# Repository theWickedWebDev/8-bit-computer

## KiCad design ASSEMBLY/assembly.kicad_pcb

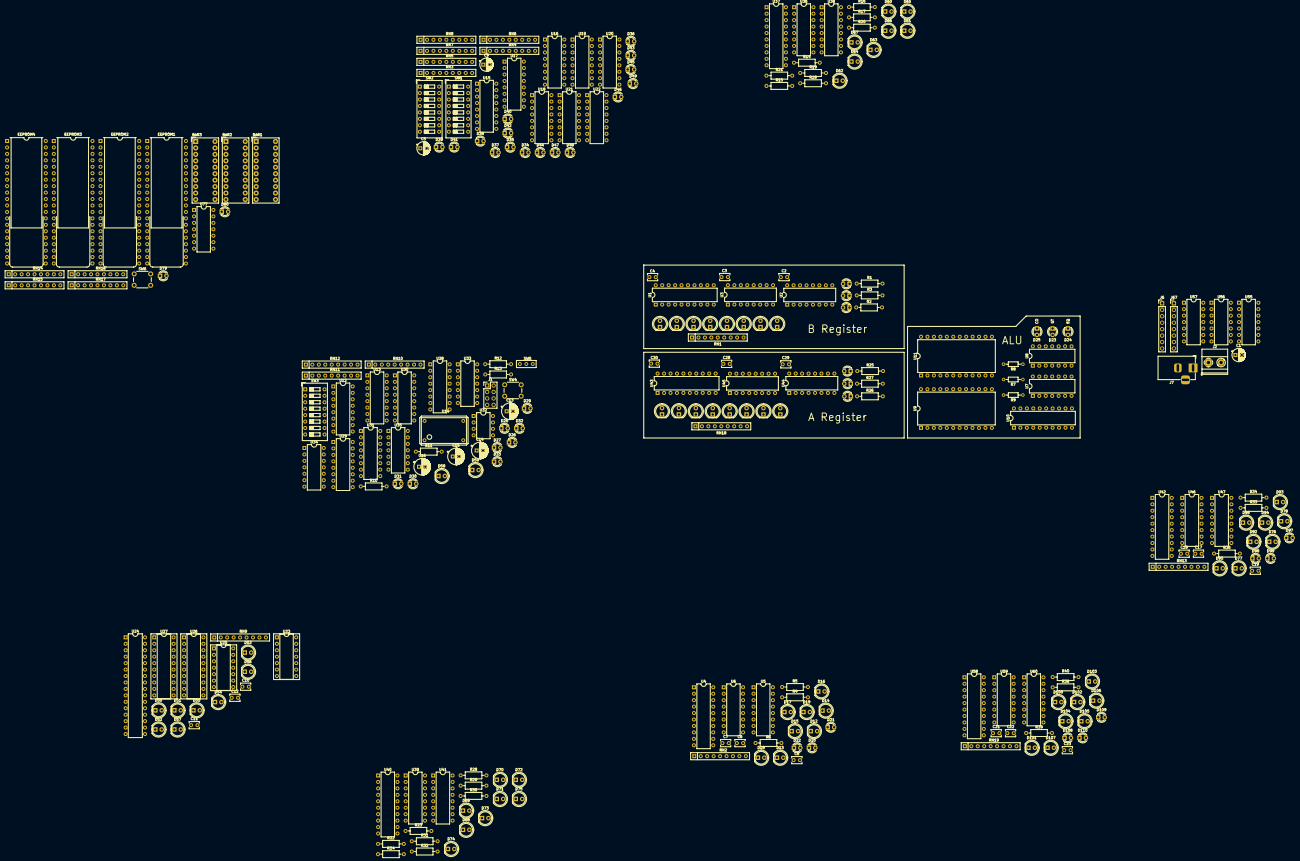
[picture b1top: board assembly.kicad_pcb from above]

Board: 2 copper layers, 264 parts (0 on the bottom side), 344 nets, no tracks yet.

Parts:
BAR1, BAR2, BAR3: HDSP-4850_2; HDSP-4850
C1, C5, C9: CP1_Small; CP_Radial_D5.0mm_P2.50mm
C2, C3, C4, C6, C7, C8, C17, C18, C19, C21, C22, C23, C28, C29, C30: CP1; C_Disc_D3.8mm_W2.6mm_P2.50mm
C10, C11, C12: C_Small; C_Disc_D3.8mm_W2.6mm_P2.50mm
C13, C14, C15, C16: CP1; CP_Radial_D6.3mm_P2.50mm
D1, D2, D3, D4, D5, D6, D7, D8, D12, D13, D14, D15, D16, D17, D18, D19, D50, D51, D52, D53, D54, D55, D56, D57, D58, D59, D60, D61, D62, D63, D64, D65, D66, D67, D68, D69, D70, D71, D72, D73, D74, D75, D76, D77, D78, D81, D82, D83, D84, D85, D86, D87, D88, D92, D93, D94, D95, D96, D100, D101, D102, D103, D104, D105, D106, D107: LED; LED_D5.0mm
D9, D10, D11, D20, D21, D22, D23, D24, D25, D26, D27, D28, D29, D30, D31, D32, D33, D34, D35, D36, D37, D38, D39, D40, D41, D42, D43, D44, D45, D46, D47, D48, D49, D79, D80, D89, D90, D91, D97, D98, D99, D108, D109, D110: LED; LED_D3.0mm
EEPROM1, EEPROM2, EEPROM3, EEPROM4: AT28C256; EEPROM_Socket_lever
J1: Conn_01x04; PinHeader_2x04_P2.54mm_Vertical
J2: Screw_Terminal_01x02; TerminalBlock_Phoenix_MKDS-1,5-2_1x02_P5.00mm_Horizontal
J6, J67: Conn_01x08; PinHeader_1x08_P2.54mm_Vertical
J7: Barrel_Jack_MountingPin; BarrelJack_Horizontal
R1, R2, R3, R4, R5, R6, R10, R11, R12, R13, R25, R26, R27, R33, R34, R35, R38, R39, R40: R_Small_US; R_Axial_DIN0207_L6.3mm_D2.5mm_P10.16mm_Horizontal
R7, R8, R9: R_Small_US; R_Axial_DIN0204_L3.6mm_D1.6mm_P7.62mm_Horizontal
R14, R15, R16, R17, R18, R19, R20, R21, R22, R23, R24, R28, R29, R30, R31, R32: R_US; R_Axial_DIN0207_L6.3mm_D2.5mm_P10.16mm_Horizontal
RN1, RN2, RN13, RN18, RN19: R_Network08; R_Array_SIP9
RN3, RN4, RN5, RN6, RN7, RN8, RN9, RN10, RN11, RN12, RN14, RN15, RN16, RN17: R_Network08_US; R_Array_SIP9
SW1, SW2, SW3: SW_DIP_x08; SW_DIP_SPSTx08_Slide_9.78x22.5mm_W7.62mm_P2.54mm
SW4, SW6: SW_Push; SW_PUSH_6mm
SW5: SW_SPDT; SPDT-SlideSwitch
U1, U4, U10, U37, U40, U42, U43, U58: 74LS245; DIP-20_W7.62mm
U2, U3, U5, U6, U12, U13, U16, U17, U20, U21, U44, U45, U46, U47, U59, U60: 74LS173; DIP-16_W7.62mm
U7, U33, U55, U56, U57, U77: 74LS04; DIP-14_W7.62mm
U8: 74LS02; DIP-14_W7.62mm
U9, U11: 74LS181; DIP-24_W15.24mm
U14: 4-pin-crystal-1mhz; full_can _1mhz_crystal
U15, U18, U19, U22: 74LS157; DIP-16_W7.62mm
U23: 74LS00; DIP-14_W7.62mm_Socket
U24: IS61C1024-15N; DIP-32_W7.62mm
U25: 74LS32; DIP-14_W7.62mm_Socket
U26, U27: 74LS245; DIP-20_W7.62mm_Socket
U28, U29, U30, U31: 74LS193; DIP-16_W7.62mm
U32: LM555xN; DIP-8_W7.62mm
U34: 74LS08; DIP-14_W7.62mm
U35: 74LS86; DIP-14_W7.62mm
U36, U38, U39, U41: 74LS161; DIP-16_W7.62mm

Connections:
/Sheet60DC0D37/MANUAL_MEM_ADR_00: RN7.2, SW2.16, U15.13
/Sheet60DC0D37/MANUAL_MEM_ADR_01: RN7.3, SW2.15, U15.10
/Sheet60DC0D37/MANUAL_MEM_ADR_02: RN7.4, SW2.14, U15.6
/Sheet60DC0D37/MANUAL_MEM_ADR_03: RN7.5, SW2.13, U15.3
/Sheet60DC0D37/MANUAL_MEM_ADR_04: RN7.6, SW2.12, U18.13
/Sheet60DC0D37/MANUAL_MEM_ADR_05: RN7.7, SW2.11, U18.10
/Sheet60DC0D37/MANUAL_MEM_ADR_06: RN7.8, SW2.10, U18.6
/Sheet60DC0D37/MANUAL_MEM_ADR_07: RN7.9, SW2.9, U18.3
/Sheet60DC0D37/MANUAL_MEM_ADR_08: RN5.2, SW1.16, U19.13
/Sheet60DC0D37/MANUAL_MEM_ADR_09: RN5.3, SW1.15, U19.10
/Sheet60DC0D37/MANUAL_MEM_ADR_10: RN5.4, SW1.14, U19.6
/Sheet60DC0D37/MANUAL_MEM_ADR_11: RN5.5, SW1.13, U19.3
/Sheet60DC0D37/MANUAL_MEM_ADR_12: RN5.6, SW1.12, U22.13
/Sheet60DC0D37/MANUAL_MEM_ADR_13: RN5.7, SW1.11, U22.10
/Sheet60DC0D37/MANUAL_MEM_ADR_14: RN5.8, SW1.10, U22.6
/Sheet60DC0D37/MANUAL_MEM_ADR_15: RN5.9, SW1.9, U22.3
/Sheet60DC0D37/MAR_00: U15.14, U21.3
/Sheet60DC0D37/MAR_01: U15.11, U21.4
/Sheet60DC0D37/MAR_02: U15.5, U21.5
/Sheet60DC0D37/MAR_03: U15.2, U21.6
/Sheet60DC0D37/MAR_04: U18.14, U20.3
/Sheet60DC0D37/MAR_05: U18.11, U20.4
/Sheet60DC0D37/MAR_06: U18.5, U20.5
/Sheet60DC0D37/MAR_07: U18.2, U20.6
/Sheet60DC0D37/MAR_08: U17.3, U19.14
/Sheet60DC0D37/MAR_09: U17.4, U19.11
/Sheet60DC0D37/MAR_10: U17.5, U19.5
/Sheet60DC0D37/MAR_11: U17.6, U19.2
/Sheet60DC0D37/MAR_12: U16.3, U22.14
/Sheet60DC0D37/MAR_13: U16.4, U22.11
/Sheet60DC0D37/MAR_14: U16.5, U22.5
/Sheet60DC0D37/MAR_15: U16.6, U22.2
/Sheet60E7756D/IO0: D57.2, U24.13, U26.18, U27.2
/Sheet60E7756D/IO1: D56.2, U24.14, U26.17, U27.3
/Sheet60E7756D/IO2: D55.2, U24.15, U26.16, U27.4
/Sheet60E7756D/IO3: D54.2, U24.17, U26.15, U27.5
/Sheet60E7756D/IO4: D53.2, U24.18, U26.14, U27.6
/Sheet60E7756D/IO5: D52.2, U24.19, U26.13, U27.7
/Sheet60E7756D/IO6: D51.2, U24.20, U26.12, U27.8
/Sheet60E7756D/IO7: D50.2, U24.21, U26.11, U27.9
/Sheet613FD1FC/D32: D80.2, EEPROM4.19, SW6.1, U77.1
/Sheet613FD1FC/STEP1: EEPROM1.10, EEPROM2.10, EEPROM3.10, EEPROM4.10, U40.9
/Sheet613FD1FC/STEP2: EEPROM1.9, EEPROM2.9, EEPROM3.9, EEPROM4.9, U40.8
/Sheet613FD1FC/STEP3: EEPROM1.8, EEPROM2.8, EEPROM3.8, EEPROM4.8, U40.7
/Sheet613FD1FC/μ28: BAR3.3, EEPROM4.15
/Sheet613FD1FC/μ29: BAR3.2, EEPROM4.16
/Sheet613FD1FC/μ30: BAR3.1, EEPROM4.17
/Sheet634DE12C/1MHz_Pulse: U12.7, U13.7, U14.8, U28.4
/Sheet634DE12C/A0: D26.2, U12.3, U28.15
/Sheet634DE12C/A1: D27.2, U12.4, U28.1
/Sheet634DE12C/A2: D28.2, U12.5, U28.10
/Sheet634DE12C/A3: D29.2, U12.6, U28.9
/Sheet634DE12C/A4: D30.2, U13.3, U29.15
/Sheet634DE12C/A5: D31.2, U13.4, U29.1
/Sheet634DE12C/A6: D32.2, U13.5, U29.10
/Sheet634DE12C/A7: D33.2, U13.6, U29.9
/μ1: BAR1.10, EEPROM1.11, U57.13
/μ2: BAR1.9, EEPROM1.12, U57.11
/μ3: BAR1.8, EEPROM1.13, U57.9
/μ4: BAR1.7, EEPROM1.15, U57.5
/μ5: BAR1.6, EEPROM1.16, U57.3
/μ6: BAR1.5, EEPROM1.17, U57.1
/μ7: BAR1.4, EEPROM1.18, U56.13
/μ8: BAR1.3, EEPROM1.19, U56.11
/μ9: BAR1.2, EEPROM2.11, U56.9
/μ10: BAR1.1, EEPROM2.12, U56.5
/μ11: BAR2.10, EEPROM2.13, U56.3
/μ12: BAR2.9, EEPROM2.15, U56.1
/μ13: BAR2.8, EEPROM2.16, U55.13
/μ14: BAR2.7, EEPROM2.17, U55.11
/μ15: BAR2.6, EEPROM2.18, U55.9
/μ16: BAR2.5, EEPROM2.19, U55.5
/μ17: BAR2.4, EEPROM3.11, U55.3
/μ18: BAR2.3, EEPROM3.12, U55.1
A0: D49.2, U15.12, U24.12
A1: D48.2, U15.9, U24.11
A2: D47.2, U15.7, U24.10
A3: D46.2, U15.4, U24.9
A4: D45.2, U18.12, U24.8
A5: D44.2, U18.9, U24.7
A6: D43.2, U18.7, U24.6
A7: D42.2, U18.4, U24.5
A8: D41.2, U19.12, U24.27
A9: D40.2, U19.9, U24.26
A10: D39.2, U19.7, U24.23
A11: D38.2, U19.4, U24.25
A12: D37.2, U22.12, U24.4
A13: D36.2, U22.9, U24.28
A14: D35.2, U22.7, U24.3
A15: D34.2, U22.4, U24.31
A16: C1.2, C2.2, C3.2, C4.2, C5.2, C6.2, C7.2, C8.2, C9.2, C10.2, C11.2, C12.2, C15.2, C16.2, C17.2, C18.2, C19.2, C21.2, C22.2, C23.2, C28.2, C29.2, C30.2, EEPROM1.4, EEPROM1.14, EEPROM1.20, EEPROM1.22, EEPROM2.4, EEPROM2.14, EEPROM2.20, EEPROM2.22, EEPROM3.4, EEPROM3.14, EEPROM3.20, EEPROM3.22, EEPROM4.4, EEPROM4.14, EEPROM4.20, EEPROM4.22, J2.1, J7.2, R1.2, R2.2, R3.2, R4.2, R5.2, R6.2, R7.2, R8.2, R9.2, R10.2, R13.2, R14.2, R15.2, R16.2, R17.2, R18.2, R19.2, R20.2, R21.2, R22.2, R23.2, R24.2, R25.2, R26.2, R27.2, R28.2, R29.2, R30.2, R31.2, R32.2, R33.2, R34.2, R35.2, R38.2, R39.2, R40.2, RN1.1, RN2.1, RN3.1, RN4.1, RN5.1, RN7.1, RN9.1, RN10.1, RN12.1, RN13.1, RN14.1, RN15.1, RN16.1, RN17.1, RN18.1, RN19.1, SW4.1, SW5.1, U1.10, U2.1, U2.2, U2.8, U3.1, U3.2, U3.8, U4.10, U5.1, U5.2, U5.8, U6.1, U6.2, U6.8, U7.7, U8.7, U9.12, U10.1, U10.10, U11.12, U12.1, U12.2, U12.8, U12.15, U13.1, U13.2, U13.8, U13.15, U14.7, U15.8, U15.15, U16.1, U16.2, U16.8, U17.1, U17.2, U17.8, U18.8, U18.15, U19.8, U19.15, U20.1, U20.2, U20.8, U21.1, U21.2, U21.8, U22.8, U22.15, U23.7, U24.2, U24.16, U24.22, U24.24, U25.7, U26.10, U27.10, U28.8, U28.14, U29.8, U29.14, U30.1, U30.8, U30.9, U30.10, U30.14, U30.15, U31.8, U31.14, U32.1, U33.7, U34.7, U35.7, U36.8, U37.1, U37.10, U38.8, U39.8, U40.1, U40.10, U40.19, U41.8, U42.10, U43.10, U44.1, U44.2, U44.8, U45.1, U45.2, U45.8, U46.1, U46.2, U46.8, U47.1, U47.2, U47.8, U55.7, U56.7, U57.7, U58.10, U59.1, U59.2, U59.8, U60.1, U60.2, U60.8, U77.7, U77.9, U77.11, U77.13
ALU0: BAR2.2, EEPROM3.13, U9.6, U11.6
ALU1: BAR2.1, EEPROM3.15, U9.5, U11.5
ALU2: BAR3.10, EEPROM3.16, U9.4, U11.4
ALU3: BAR3.9, EEPROM3.17, U9.3, U11.3
ALU_MODE: BAR3.8, EEPROM3.18, U9.8, U11.8
ALU_OUT: U10.19, U56.2
A_IN: BAR3.5, D10.2, D21.2, D90.2, D98.2, D109.2, U2.9, U2.10, U3.9, U3.10, U5.9, U5.10, U6.9, U6.10, U44.9, U44.10, U45.9, U45.10, U46.9, U46.10, U47.9, U47.10, U55.8, U56.4, U56.8, U57.8, U59.9, U59.10, U60.9, U60.10, U77.4
A_OUT: BAR3.4, D11.2, D22.2, D91.2, D99.2, D110.2, U1.19, U4.19, U42.19, U43.19, U55.10, U56.6, U56.10, U57.10, U58.19, U77.6
BUS0: J6.1, J67.1, RN10.2, SW3.16, U1.11, U3.11, U4.11, U6.11, U10.9, U12.14, U17.14, U21.14, U27.18, U38.3, U41.3, U42.11, U43.11, U45.11, U47.11, U58.11, U60.11
BUS1: J6.2, J67.2, RN10.3, SW3.15, U1.12, U3.12, U4.12, U6.12, U10.8, U12.13, U17.13, U21.13, U27.17, U38.4, U41.4, U42.12, U43.12, U45.12, U47.12, U58.12, U60.12
BUS2: J6.3, J67.3, RN10.4, SW3.14, U1.13, U3.13, U4.13, U6.13, U10.7, U12.12, U17.12, U21.12, U27.16, U38.5, U41.5, U42.13, U43.13, U45.13, U47.13, U58.13, U60.13
BUS3: J6.4, J67.4, RN10.5, SW3.13, U1.14, U3.14, U4.14, U6.14, U10.6, U12.11, U17.11, U21.11, U27.15, U38.6, U41.6, U42.14, U43.14, U45.14, U47.14, U58.14, U60.14
BUS4: J6.5, J67.5, RN10.6, SW3.12, U1.15, U2.11, U4.15, U5.11, U10.5, U13.14, U16.14, U20.14, U27.14, U36.6, U39.3, U42.15, U43.15, U44.11, U46.11, U58.15, U59.11
BUS5: J6.6, J67.6, RN10.7, SW3.11, U1.16, U2.12, U4.16, U5.12, U10.4, U13.13, U16.13, U20.13, U27.13, U36.5, U39.4, U42.16, U43.16, U44.12, U46.12, U58.16, U59.12
BUS6: J6.7, J67.7, RN10.8, SW3.10, U1.17, U2.13, U4.17, U5.13, U10.3, U13.12, U16.12, U20.12, U27.12, U36.4, U39.5, U42.17, U43.17, U44.13, U46.13, U58.17, U59.13
BUS7: J6.8, J67.8, RN10.9, SW3.9, U1.18, U2.14, U4.18, U5.14, U10.2, U13.11, U16.11, U20.11, U27.11, U36.3, U39.6, U42.18, U43.18, U44.14, U46.14, U58.18, U59.14
CARRY: D25.2, EEPROM1.5, EEPROM2.5, EEPROM3.5, EEPROM4.5, U7.2
CLOCK: D59.2, U2.7, U3.7, U5.7, U6.7, U16.7, U17.7, U20.7, U21.7, U25.2, U35.3, U36.2, U38.2, U39.2, U41.2, U44.7, U45.7, U46.7, U47.7, U59.7, U60.7
D0: D1.2, D12.2, D76.2, D81.2, D100.2, EEPROM1.3, EEPROM2.3, EEPROM3.3, EEPROM4.3, U1.9, U3.6, U4.9, U6.6, U11.1, U11.2, U26.2, U42.9, U43.9, U45.6, U47.6, U58.9, U60.6
D1: D2.2, D13.2, D77.2, D82.2, D101.2, EEPROM1.25, EEPROM2.25, EEPROM3.25, EEPROM4.25, U1.8, U3.5, U4.8, U6.5, U11.22, U11.23, U26.3, U42.8, U43.8, U45.5, U47.5, U58.8, U60.5
D2: D3.2, D14.2, D78.2, D83.2, D102.2, EEPROM1.24, EEPROM2.24, EEPROM3.24, EEPROM4.24, U1.7, U3.4, U4.7, U6.4, U11.20, U11.21, U26.4, U42.7, U43.7, U45.4, U47.4, U58.7, U60.4
D3: D4.2, D15.2, D84.2, D92.2, D103.2, EEPROM1.21, EEPROM2.21, EEPROM3.21, EEPROM4.21, U1.6, U3.3, U4.6, U6.3, U11.18, U11.19, U26.5, U42.6, U43.6, U45.3, U47.3, U58.6, U60.3
D4: D5.2, D16.2, D85.2, D93.2, D104.2, EEPROM1.23, EEPROM2.23, EEPROM3.23, EEPROM4.23, U1.5, U2.6, U4.5, U5.6, U9.1, U9.2, U26.6, U42.5, U43.5, U44.6, U46.6, U58.5, U59.6
D5: D6.2, D17.2, D86.2, D94.2, D105.2, EEPROM1.2, EEPROM2.2, EEPROM3.2, EEPROM4.2, U1.4, U2.5, U4.4, U5.5, U9.22, U9.23, U26.7, U42.4, U43.4, U44.5, U46.5, U58.4, U59.5
D6: D7.2, D18.2, D87.2, D95.2, D106.2, EEPROM1.26, EEPROM2.26, EEPROM3.26, EEPROM4.26, U1.3, U2.4, U4.3, U5.4, U9.20, U9.21, U26.8, U42.3, U43.3, U44.4, U46.4, U58.3, U59.4
D7: D8.2, D19.2, D88.2, D96.2, D107.2, EEPROM1.1, EEPROM2.1, EEPROM3.1, EEPROM4.1, U1.2, U2.3, U4.2, U5.3, U9.18, U9.19, U26.9, U42.2, U43.2, U44.3, U46.3, U58.2, U59.3
EQ: D24.2, EEPROM1.6, EEPROM2.6, EEPROM3.6, EEPROM4.6, U8.6, U9.14, U11.14
GT: D23.2, EEPROM1.7, EEPROM2.7, EEPROM3.7, EEPROM4.7, U8.4
HALT: D79.2, EEPROM4.18, U34.5, U34.9
MAR1_IN: U16.9, U16.10, U17.9, U17.10, U57.4
MAR2_IN: U20.9, U20.10, U21.9, U21.10, U57.2
unnamed: BAR1.11, RN14.9
unnamed: BAR1.12, RN14.8
unnamed: BAR1.13, RN14.7
unnamed: BAR1.14, RN14.6
unnamed: BAR1.15, RN14.5
unnamed: BAR1.16, RN14.4
unnamed: BAR1.17, RN14.3
unnamed: BAR1.18, RN14.2
unnamed: BAR1.19, RN15.9
unnamed: BAR1.20, RN15.8
unnamed: BAR2.11, RN15.7
unnamed: BAR2.12, RN15.6
unnamed: BAR2.13, RN15.5
unnamed: BAR2.14, RN15.4
unnamed: BAR2.15, RN15.3
unnamed: BAR2.16, RN15.2
unnamed: BAR2.17, RN16.9
unnamed: BAR2.18, RN16.8
unnamed: BAR2.19, RN16.7
unnamed: BAR2.20, RN16.6
unnamed: BAR3.11, RN16.5
unnamed: BAR3.12, RN16.4
unnamed: BAR3.13, RN16.3
unnamed: BAR3.14, RN16.2
unnamed: BAR3.15, RN17.9
unnamed: BAR3.16, RN17.8
unnamed: BAR3.17, RN17.7
unnamed: BAR3.18, RN17.6
unnamed: BAR3.19, RN17.5
unnamed: BAR3.20, RN17.4
unnamed: C13.2, U32.5
unnamed: C14.2, R11.1, U32.6, U32.7
unnamed: D1.1, RN1.9
unnamed: D2.1, RN1.8
unnamed: D3.1, RN1.7
unnamed: D4.1, RN1.6
unnamed: D5.1, RN1.5
unnamed: D6.1, RN1.4
unnamed: D7.1, RN1.3
unnamed: D8.1, RN1.2
unnamed: D9.1, R1.1
unnamed: D10.1, R2.1
unnamed: D11.1, R3.1
unnamed: D12.1, RN2.9
unnamed: D13.1, RN2.8
unnamed: D14.1, RN2.7
unnamed: D15.1, RN2.6
unnamed: D16.1, RN2.5
unnamed: D17.1, RN2.4
unnamed: D18.1, RN2.3
unnamed: D19.1, RN2.2
unnamed: D20.1, R4.1
unnamed: D21.1, R5.1
unnamed: D22.1, R6.1
unnamed: D23.1, R7.1
unnamed: D24.1, R8.1
unnamed: D25.1, R9.1
unnamed: D26.1, RN12.2
unnamed: D27.1, RN12.3
unnamed: D28.1, RN12.4
unnamed: D29.1, RN12.5
unnamed: D30.1, RN12.6
unnamed: D31.1, RN12.7
unnamed: D32.1, RN12.8
unnamed: D33.1, RN12.9
unnamed: D34.1, RN3.9
unnamed: D35.1, RN3.8
unnamed: D36.1, RN3.7
unnamed: D37.1, RN3.6
unnamed: D38.1, RN3.5
unnamed: D39.1, RN3.4
unnamed: D40.1, RN3.3
unnamed: D41.1, RN3.2
unnamed: D42.1, RN4.9
unnamed: D43.1, RN4.8
unnamed: D44.1, RN4.7
unnamed: D45.1, RN4.6
unnamed: D46.1, RN4.5
unnamed: D47.1, RN4.4
unnamed: D48.1, RN4.3
unnamed: D49.1, RN4.2
unnamed: D50.1, RN9.9
unnamed: D51.1, RN9.8
unnamed: D52.1, RN9.7
unnamed: D53.1, RN9.6
unnamed: D54.1, RN9.5
unnamed: D55.1, RN9.4
unnamed: D56.1, RN9.3
unnamed: D57.1, RN9.2
unnamed: D58.1, R10.1
unnamed: D58.2, SW5.2, U33.1, U34.12
unnamed: D59.1, R13.1
unnamed: D60.1, R14.1
unnamed: D60.2, U36.11, U37.18
unnamed: D61.1, R15.1
unnamed: D61.2, U36.12, U37.17
unnamed: D62.1, R16.1
unnamed: D62.2, U36.13, U37.16
unnamed: D63.1, R17.1
unnamed: D63.2, U36.14, U37.15
unnamed: D64.1, R18.1
unnamed: D64.2, U37.14, U38.11
unnamed: D65.1, R19.1
unnamed: D65.2, U37.13, U38.12
unnamed: D66.1, R20.1
unnamed: D66.2, U37.12, U38.13
unnamed: D67.1, R21.1
unnamed: D67.2, U37.11, U38.14
unnamed: D68.1, R22.1
unnamed: D68.2, U39.11, U40.18
unnamed: D69.1, R23.1
unnamed: D69.2, U39.12, U40.17
unnamed: D70.1, R24.1
unnamed: D70.2, U39.13, U40.16
unnamed: D71.1, R28.1
unnamed: D71.2, U39.14, U40.15
unnamed: D72.1, R29.1
unnamed: D72.2, U40.14, U41.11
unnamed: D73.1, R30.1
unnamed: D73.2, U40.13, U41.12
unnamed: D74.1, R31.1
unnamed: D74.2, U40.12, U41.13
unnamed: D75.1, R32.1
unnamed: D75.2, U40.11, U41.14
unnamed: D76.1, RN13.9
unnamed: D77.1, RN13.8
unnamed: D78.1, RN13.7
unnamed: D79.1, RN17.3
unnamed: D80.1, RN17.2
unnamed: D81.1, RN18.9
unnamed: D82.1, RN18.8
unnamed: D83.1, RN18.7
unnamed: D84.1, RN18.6
unnamed: D85.1, RN18.5
unnamed: D86.1, RN18.4
unnamed: D87.1, RN18.3
unnamed: D88.1, RN18.2
unnamed: D89.1, R25.1
unnamed: D90.1, R26.1
unnamed: D91.1, R27.1
unnamed: D92.1, RN13.6
unnamed: D93.1, RN13.5
unnamed: D94.1, RN13.4
unnamed: D95.1, RN13.3
unnamed: D96.1, RN13.2
unnamed: D97.1, R33.1
unnamed: D98.1, R34.1
unnamed: D99.1, R35.1
unnamed: D100.1, RN19.9
unnamed: D101.1, RN19.8
unnamed: D102.1, RN19.7
unnamed: D103.1, RN19.6
unnamed: D104.1, RN19.5
unnamed: D105.1, RN19.4
unnamed: D106.1, RN19.3
unnamed: D107.1, RN19.2
unnamed: D108.1, R38.1
unnamed: D109.1, R39.1
unnamed: D110.1, R40.1
unnamed: EEPROM4.12, U77.3
unnamed: EEPROM4.13, U77.5
unnamed: J1.1, J1.3, J1.5, J1.7, U34.13
unnamed: J1.2, U31.3
unnamed: J1.4, U31.2
unnamed: J1.6, U31.6
unnamed: J1.8, U31.7
unnamed: R12.2, SW4.2, U32.2
unnamed: RN6.2, SW1.8
unnamed: RN6.3, SW1.7
unnamed: RN6.4, SW1.6
unnamed: RN6.5, SW1.5
unnamed: RN6.6, SW1.4
unnamed: RN6.7, SW1.3
unnamed: RN6.8, SW1.2
unnamed: RN6.9, SW1.1
unnamed: RN8.2, SW2.8
unnamed: RN8.3, SW2.7
unnamed: RN8.4, SW2.6
unnamed: RN8.5, SW2.5
unnamed: RN8.6, SW2.4
unnamed: RN8.7, SW2.3
unnamed: RN8.8, SW2.2
unnamed: RN8.9, SW2.1
unnamed: RN11.2, SW3.8
unnamed: RN11.3, SW3.7
unnamed: RN11.4, SW3.6
unnamed: RN11.5, SW3.5
unnamed: RN11.6, SW3.4
unnamed: RN11.7, SW3.3
unnamed: RN11.8, SW3.2
unnamed: RN11.9, SW3.1
unnamed: U7.1, U8.5, U9.16
unnamed: U10.11, U11.9
unnamed: U10.12, U11.10
unnamed: U10.13, U11.11
unnamed: U10.14, U11.13
unnamed: U9.9, U10.15
unnamed: U9.10, U10.16
unnamed: U9.11, U10.17
unnamed: U9.13, U10.18
unnamed: U9.7, U11.16
unnamed: U23.1, U25.3
unnamed: U23.3, U24.29, U26.19
unnamed: U28.11, U29.11, U30.11, U30.13, U31.5
unnamed: U28.13, U29.4
unnamed: U29.13, U30.4
unnamed: U32.3, U34.1
unnamed: U33.2, U34.2
unnamed: U34.3, U34.4
unnamed: U34.6, U35.1
unnamed: U34.8, U35.2
unnamed: U34.10, U34.11
unnamed: U36.10, U38.15
unnamed: U39.10, U41.15
OUTPUT_ENABLE: U27.19, U56.12
PC_JUMP: U36.9, U38.9, U57.12
PC_OE: U37.19, U57.6
PROG: BAR3.7, EEPROM3.19, U15.1, U18.1, U19.1, U22.1, U25.1
RAM_WR: BAR3.6, EEPROM4.11, U23.2
RESET: D9.2, D20.2, D89.2, D97.2, D108.2, U2.15, U3.15, U5.15, U6.15, U16.15, U17.15, U20.15, U21.15, U36.1, U38.1, U39.1, U41.1, U44.15, U45.15, U46.15, U47.15, U59.15, U60.15, U77.2
SET_FREQ: U12.9, U12.10, U13.9, U13.10, U55.12
VCC: C1.1, C2.1, C3.1, C4.1, C5.1, C6.1, C7.1, C8.1, C9.1, C10.1, C11.1, C12.1, C13.1, C14.1, C15.1, C16.1, C17.1, C18.1, C19.1, C21.1, C22.1, C23.1, C28.1, C29.1, C30.1, EEPROM1.27, EEPROM1.28, EEPROM2.27, EEPROM2.28, EEPROM3.27, EEPROM3.28, EEPROM4.27, EEPROM4.28, J2.2, J7.1, R11.2, R12.1, RN6.1, RN8.1, RN11.1, SW5.3, SW6.2, U1.1, U1.20, U2.16, U3.16, U4.1, U4.20, U5.16, U6.16, U7.14, U8.14, U9.24, U10.20, U11.7, U11.24, U12.16, U13.16, U14.14, U15.16, U16.16, U17.16, U18.16, U19.16, U20.16, U21.16, U22.16, U23.14, U24.30, U24.32, U25.14, U26.1, U26.20, U27.1, U27.20, U28.5, U28.16, U29.5, U29.16, U30.5, U30.16, U31.4, U31.11, U31.16, U32.4, U32.8, U33.14, U34.14, U35.14, U36.7, U36.16, U37.20, U38.7, U38.10, U38.16, U39.7, U39.9, U39.16, U40.20, U41.7, U41.9, U41.10, U41.16, U42.1, U42.20, U43.1, U43.20, U44.16, U45.16, U46.16, U47.16, U55.14, U56.14, U57.14, U58.1, U58.20, U59.16, U60.16, U77.14

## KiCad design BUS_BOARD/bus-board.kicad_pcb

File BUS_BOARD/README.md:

# BUS Board

MORE DETAILS TO COME

Made a board to help me while testing the modular components. It pulls the lines LOW as well as has 8 LED status indicator lights.

## QA
✅ Tested this module and verified it works as expected

### Changes if I re-fabricate this again

- Perhaps I would want to include all the `74LS245` chips from other modules onto this board instead.
- Resize this board so that (perhaps) I could place this underneath all the other modules and be able to plug them into this board directly - instead of using jumper wires.

## PCB & Schematics

<br/>

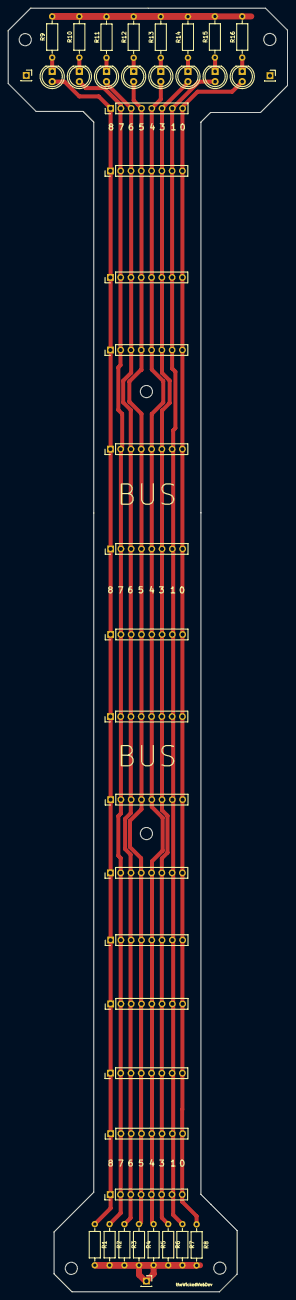
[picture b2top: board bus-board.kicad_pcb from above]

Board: 2 copper layers, 69.0 x 317.0 mm, 42 parts (0 on the bottom side), 17 nets.

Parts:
D1, D2, D3, D4, D5, D6, D7, D8: LED; LED_D5.0mm
J1, J2, J3, J4, J5, J6, J7, J8, J9, J10, J12, J13, J14, J15, J16: Conn_01x08; PinHeader_1x08_P2.54mm_Vertical
J11, J17, J18: Conn_01x01; PinSocket_1x01_P2.54mm_Vertical
R1, R2, R3, R4, R5, R6, R7, R8, R9, R10, R11, R12, R13, R14, R15, R16: R_Small_US; R_Axial_DIN0207_L6.3mm_D2.5mm_P10.16mm_Horizontal

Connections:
GND: J11.1, J17.1, J18.1, R1.2, R2.2, R3.2, R4.2, R5.2, R6.2, R7.2, R8.2, R9.2, R10.2, R11.2, R12.2, R13.2, R14.2, R15.2, R16.2
unnamed: D1.1, R9.1
unnamed: D1.2, J1.1, J2.1, J3.1, J4.1, J5.1, J6.1, J7.1, J8.1, J9.1, J10.1, J12.1, J13.1, J14.1, J15.1, J16.1, R1.1
unnamed: D2.1, R10.1
unnamed: D2.2, J1.2, J2.2, J3.2, J4.2, J5.2, J6.2, J7.2, J8.2, J9.2, J10.2, J12.2, J13.2, J14.2, J15.2, J16.2, R2.1
unnamed: D3.1, R11.1
unnamed: D3.2, J1.3, J2.3, J3.3, J4.3, J5.3, J6.3, J7.3, J8.3, J9.3, J10.3, J12.3, J13.3, J14.3, J15.3, J16.3, R3.1
unnamed: D4.1, R12.1
unnamed: D4.2, J1.4, J2.4, J3.4, J4.4, J5.4, J6.4, J7.4, J8.4, J9.4, J10.4, J12.4, J13.4, J14.4, J15.4, J16.4, R4.1
unnamed: D5.1, R13.1
unnamed: D5.2, J1.5, J2.5, J3.5, J4.5, J5.5, J6.5, J7.5, J8.5, J9.5, J10.5, J12.5, J13.5, J14.5, J15.5, J16.5, R5.1
unnamed: D6.1, R14.1
unnamed: D6.2, J1.6, J2.6, J3.6, J4.6, J5.6, J6.6, J7.6, J8.6, J9.6, J10.6, J12.6, J13.6, J14.6, J15.6, J16.6, R6.1
unnamed: D7.1, R15.1
unnamed: D7.2, J1.7, J2.7, J3.7, J4.7, J5.7, J6.7, J7.7, J8.7, J9.7, J10.7, J12.7, J13.7, J14.7, J15.7, J16.7, R7.1
unnamed: D8.1, R16.1
unnamed: D8.2, J1.8, J2.8, J3.8, J4.8, J5.8, J6.8, J7.8, J8.8, J9.8, J10.8, J12.8, J13.8, J14.8, J15.8, J16.8, R8.1

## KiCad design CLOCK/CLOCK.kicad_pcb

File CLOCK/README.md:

# Clock v3.1

KiCad Files, images and Gerber files are included.

### Description
This is a build for a computer clock module. It has two modes, `run`, which takes advantage of a *full-can quartz oscillating crystal*, and `manual`, which is a *monostable circuit* built with a *555 timer*.

## Manual (Monostable)

While in `manual mode`, the clock will pulse only when the manual button is pressed. This button is *debounced* through the 555 timer with a capacitor & resistor.

#### Formula

The formula to calculate the debounce time is:
```
1.1 * R * C
```

*ie. 1.1 * 47μf * 4KΩ = 206 (0.2 seconds)*

## Run (Astable)

This circuit continuously sends a clock pulse out. The starting frequency is the value of the `Quartz Crystal` (in my case, 1Mhz). 

The square wave from the crystal goes into the first `74LS193` Up/Down Counter. This counter is chained in series through 3 other `74LS193` counters. They are wired up to produce a single, divided-by, clock pulse.

There are 2 inputs, `A0..A7`, and `Freq. Tuning`. The data latched into `A0..A7` is sent to the 2nd, and 3rd counters, whereas the `Freq. Tuning` input is connected to the outputs of the 4th(last) counter in the series.

You can use a 2-pin jumper to chose which tuning you'd like.

<br/>
<hr/>
<br/>

## QA & Assembly

<br/>

## PCB Fabrication
I use www.jlcpcb.com for my circuit board manufacturing. They print 5 copies of each order. This order cost me `$9.50`

<br/>

### Schematic

<br/>

### Rendering

<br/>

<br/>

### Fritzing Breadboard
(Might not be 100% accurate)

<br/>
<hr/>
<br/>

## Parts List

### IC's
- `555` (1) - 555 Timer [Datasheet/Product](https://www.jameco.com/z/NE555P-Major-Brands-IC-LM555P-Single-Timer-LM555CN-NE555N-TL555P-MC1455P-_27422.html)

- `74LS173` (2) - 4-bit D-type Tri-state, Registers [Datasheet/Product](https://www.jameco.com/z/74LS173-Major-Brands-IC-74LS173-4-BIT-D-TYPE-REGISTER-3-STATE-OUTPUT_46922.html)

- `74LS193` (4) - Up/Down MOD-16 Binary Counter [Datasheet/Product](https://www.jameco.com/z/74LS193-Major-Brands-IC-74LS193-Synchronous-4-Bit-Up-Down-Binary-Counter_47036.html)

- `74LS08` (1) - Quad 2-input AND gate [Datasheet/Product](https://www.jameco.com/z/74LS08-Major-Brands-IC-74LS08-Quad-2-Input-Positive-AND-Gate_46375.html)

- `74LS04` (1) - HEX Inverter [Datasheet/Product](https://www.jameco.com/z/74LS04-Major-Brands-IC-74LS04-Hex-Inverter_46316.html)

- `74LS86` (1) - QUAD 2-input XOR gate [Datasheet/Product](https://www.jameco.com/z/74LS86-Major-Brands-IC-74LS86-QUAD-2-INPUT-EXCLUSIVE-OR-GATE_48098.html)

### Passive & Other
<br/>

- `1Mhz Full Can Crystal` (1) [Datasheet/Product](https://www.jameco.com/z/OSC1-Jameco-Valuepro-1-MHz-Full-Can-Crystal-Oscillator_27861.html)

- `47uf Capacitor` (1) Polarized
- `22uf Capacitor` (1) Polarized
- `100uf Capacitor` (2) Polarized (Decoupling)

- `4kΩ Resistor` (1)
- `1kΩ Resistor` (2) Pull-up Resistors
- `1.5kΩ Resistor` (2) Current limiting resistors for LEDs

- `Screw Terminal` (1) - 2pin Terminal [Datasheet/Product](https://www.jameco.com/z/EK500V-02P-R-Dinkle-Terminal-Block-Header-2-Position-Top-Screw-5mm-Solder-Straight-Thru-Hole-20A_160785.html)

- `8 Pin Switch` (1) - DIP 8-pin switch [Datasheet/Product](https://www.jameco.com/z/76SB08ST-Grayhill-DIP-Switch-On-Off-Single-Pole-Single-Throw-8-Raised-Rocker-0-15-Amp-30-Volt-PC-Pins-2000-Cycle-2-5mm-Through-Hole-Tube_696917.html)

- `Tactile SPST Button` (2) - Button [Datasheet/Product](https://www.jameco.com/z/JTP1230A-Apem-Components-Switch-Push-Button-Tactile-Single-Pole-Single-Throw-Off-Momentary-On-15-Volt-DC-20mA_1586074.html)

- `Slide SPDR Switch` (2) - SPDT 3-pin Switch [Datasheet/Product](https://www.jameco.com/z/EG218-E-Switch-Slide-Switch-SPDT-ON-ON-500mA-50VDC-3-Pin-Breadboard-Friendly_2314127.html)

- `5mm LEDs` (2)
- `3mm LEDs` (8)
- `Pin Header 1x8` (2)
- `Pin Header 1x2` (1)
- `Pin Header 2x4` (1)

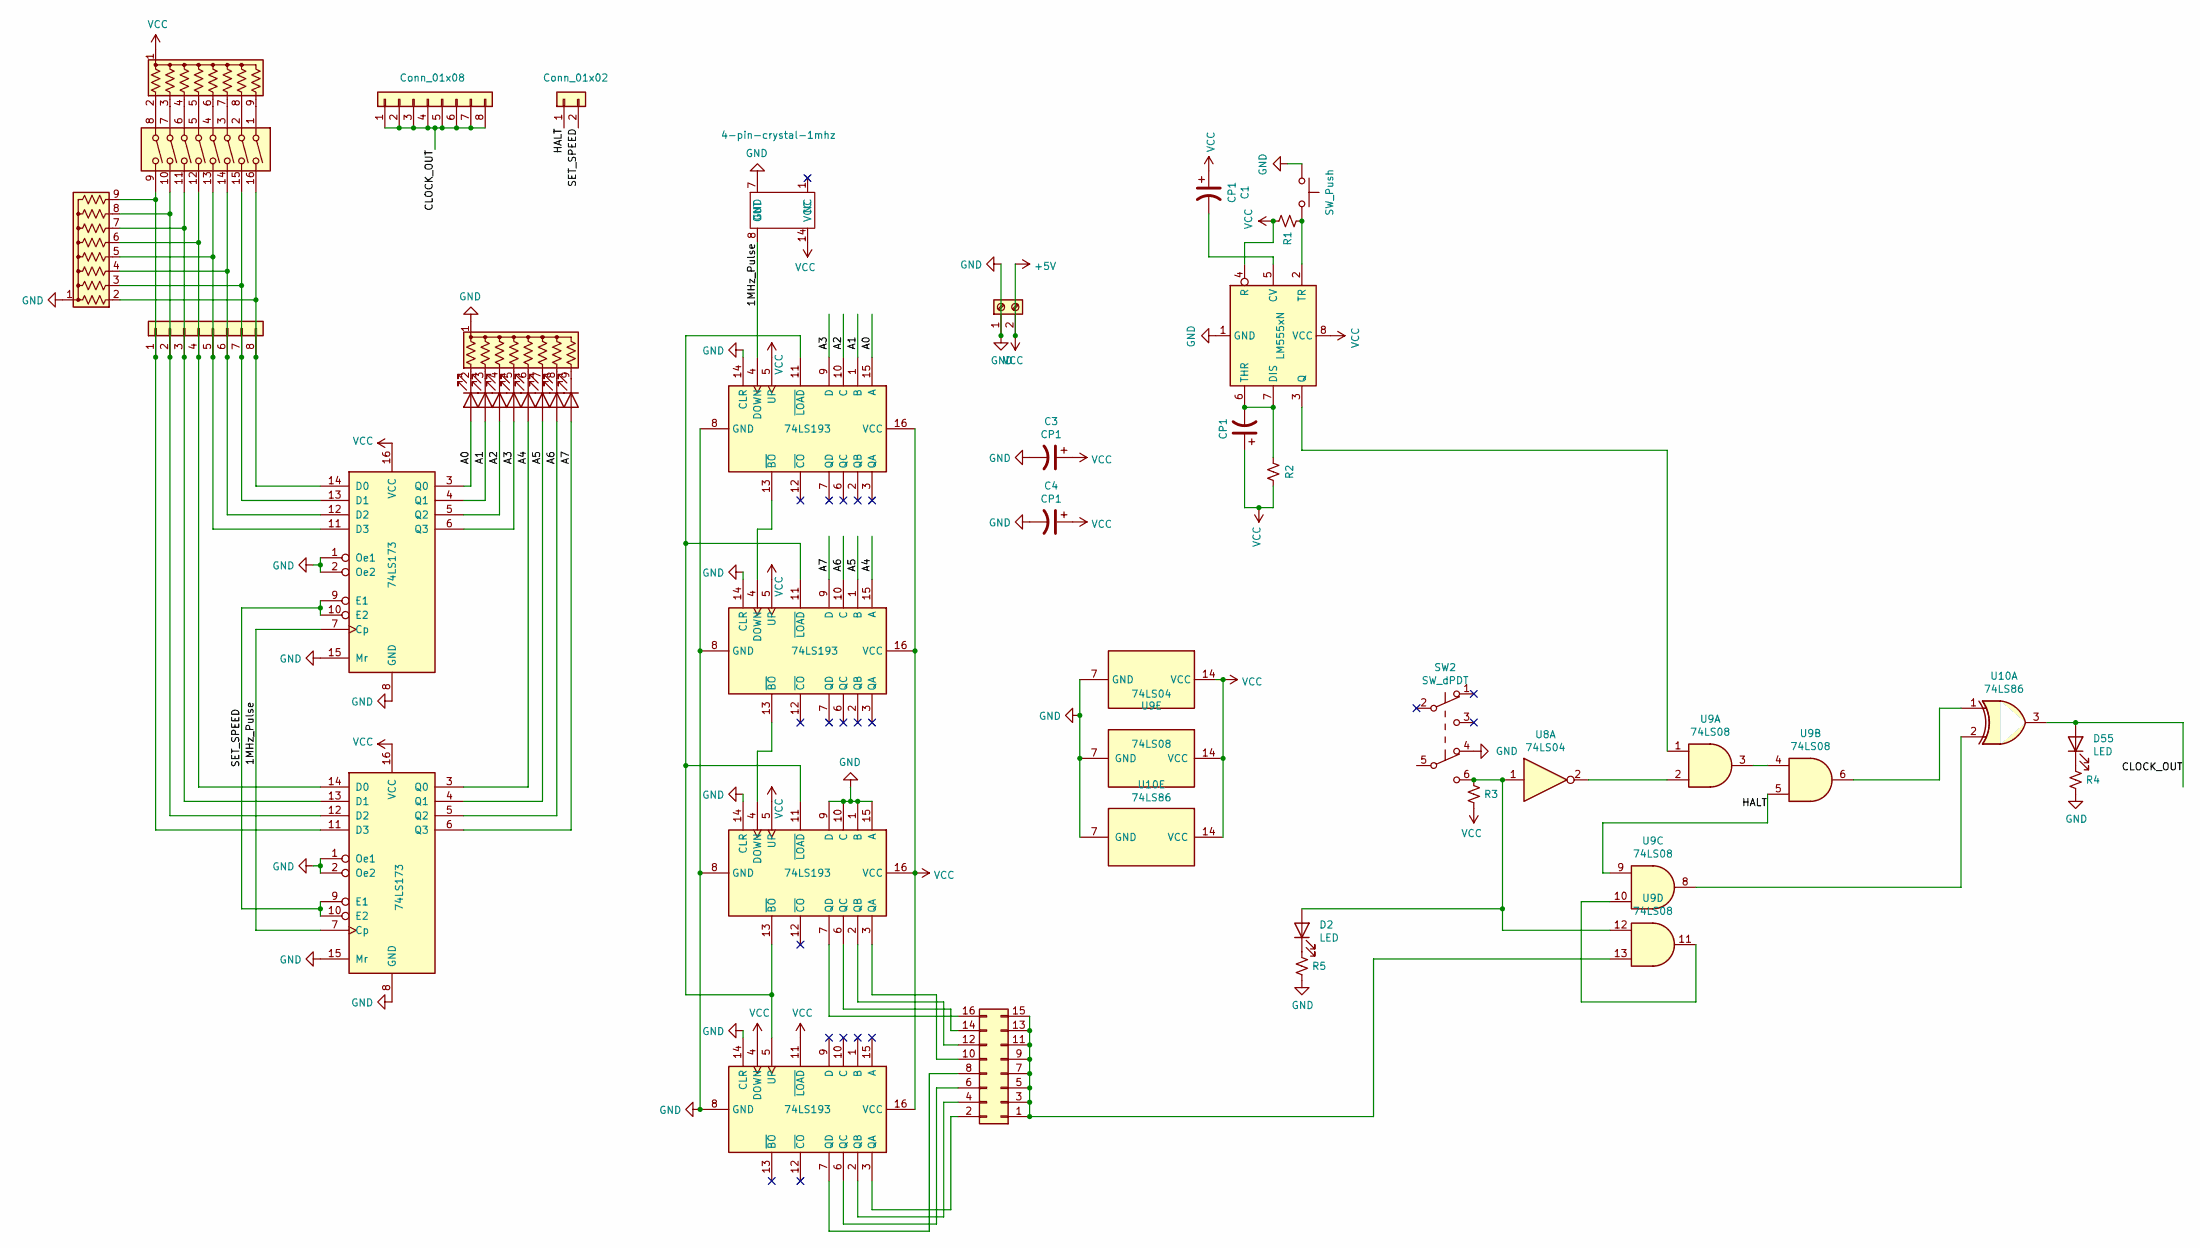
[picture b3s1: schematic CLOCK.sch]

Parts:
C1, C2, C3, C4: CP1; CP_Radial_D6.3mm_P2.50mm
D1, D3, D4, D5, D6, D7, D8, D54: LED; LED_D3.0mm
D2, D55: LED; LED_D5.0mm
J1: Screw_Terminal_01x02; TerminalBlock_Phoenix_MKDS-1,5-2_1x02_P5.00mm_Horizontal
J2, J5: Conn_01x08; PinHeader_1x08_P2.54mm_Vertical
J3: Conn_01x02; PinHeader_1x02_P2.54mm_Vertical
J34: Conn_01x08; PinHeader_2x08_P2.54mm_Vertical
R1, R2, R3, R4, R5: R_Small_US; R_Axial_DIN0207_L6.3mm_D2.5mm_P10.16mm_Horizontal
RN1, RN2, RN3: R_Network08_US; R_Array_SIP9
SW1: SW_Push; SW_PUSH_6mm
SW2: SW_dPDT; dpdt_tht_push_switch
SW13: SW_DIP_x08; SW_DIP_SPSTx08_Slide_9.78x22.5mm_W7.62mm_P2.54mm
U1: 4-pin-crystal-1mhz; full_can _1mhz_crystal
U2, U4, U5, U6: 74LS193; DIP-16_W7.62mm
U3, U11: 74LS173; DIP-16_W7.62mm
U7: LM555xN; DIP-8_W7.62mm
U8: 74LS04; DIP-14_W7.62mm
U9: 74LS08; DIP-14_W7.62mm
U10: 74LS86; DIP-14_W7.62mm

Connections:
+5V: C1.1, C2.1, C3.1, C4.1, J1.2, R1.1, R2.2, R3.2, RN2.1 (common), U1.14 (VCC), U2.5 (UP), U2.16 (VCC), U3.16 (VCC), U4.5 (UP), U4.16 (VCC), U5.5 (UP), U5.16 (VCC), U6.4 (DOWN), U6.11 (~LOAD), U6.16 (VCC), U7.4 (R), U7.8 (VCC), U8.14 (VCC), U9.14 (VCC), U10.14 (VCC), U11.16 (VCC)
/1MHz_Pulse: U1.8 (OUT), U2.4 (DOWN), U3.7 (Cp), U11.7 (Cp)
/A0: D1.2 (A), U2.15 (A), U3.3 (Q0)
/A1: D54.2 (A), U2.1 (B), U3.4 (Q1)
/A2: D3.2 (A), U2.10 (C), U3.5 (Q2)
/A3: D4.2 (A), U2.9 (D), U3.6 (Q3)
/A4: D5.2 (A), U4.15 (A), U11.3 (Q0)
/A5: D6.2 (A), U4.1 (B), U11.4 (Q1)
/A6: D7.2 (A), U4.10 (C), U11.5 (Q2)
/A7: D8.2 (A), U4.9 (D), U11.6 (Q3)
/CLOCK_OUT: D55.2 (A), J5.1, J5.2, J5.3, J5.4, J5.5, J5.6, J5.7, J5.8, U10.3
/HALT: J3.1, U9.5, U9.9
/SET_SPEED: J3.2, U3.9 (E1), U3.10 (E2), U11.9 (E1), U11.10 (E2)
GND: C3.2, C4.2, J1.1, R4.2, R5.2, RN1.1 (common), RN3.1 (common), SW1.1, SW2.4 (A), U1.7 (GND), U2.8 (GND), U2.14 (CLR), U3.1 (Oe1), U3.2 (Oe2), U3.8 (GND), U3.15 (Mr), U4.8 (GND), U4.14 (CLR), U5.1 (B), U5.8 (GND), U5.9 (D), U5.10 (C), U5.14 (CLR), U5.15 (A), U6.8 (GND), U6.14 (CLR), U7.1 (GND), U8.7 (GND), U9.7 (GND), U10.7 (GND), U11.1 (Oe1), U11.2 (Oe2), U11.8 (GND), U11.15 (Mr)
unnamed: C1.2, U7.5 (CV)
unnamed: C2.2, R2.1, U7.6 (THR), U7.7 (DIS)
unnamed: D1.1 (K), RN3.2 (R1)
unnamed: D2.1 (K), R5.1
unnamed: D2.2 (A), R3.1, SW2.6 (C), U8.1, U9.12
unnamed: D3.1 (K), RN3.4 (R3)
unnamed: D4.1 (K), RN3.5 (R4)
unnamed: D5.1 (K), RN3.6 (R5)
unnamed: D6.1 (K), RN3.7 (R6)
unnamed: D7.1 (K), RN3.8 (R7)
unnamed: D8.1 (K), RN3.9 (R8)
unnamed: D54.1 (K), RN3.3 (R2)
unnamed: D55.1 (K), R4.1
unnamed: J2.1, RN1.9 (R8), SW13.9, U11.11 (D3)
unnamed: J2.2, RN1.8 (R7), SW13.10, U11.12 (D2)
unnamed: J2.3, RN1.7 (R6), SW13.11, U11.13 (D1)
unnamed: J2.4, RN1.6 (R5), SW13.12, U11.14 (D0)
unnamed: J2.5, RN1.5 (R4), SW13.13, U3.11 (D3)
unnamed: J2.6, RN1.4 (R3), SW13.14, U3.12 (D2)
unnamed: J2.7, RN1.3 (R2), SW13.15, U3.13 (D1)
unnamed: J2.8, RN1.2 (R1), SW13.16, U3.14 (D0)
unnamed: J34.1, J34.3, J34.5, J34.7, J34.9, J34.11, J34.13, J34.15, U9.13
unnamed: J34.2, U6.3 (QA)
unnamed: J34.4, U6.2 (QB)
unnamed: J34.6, U6.6 (QC)
unnamed: J34.8, U6.7 (QD)
unnamed: J34.10, U5.3 (QA)
unnamed: J34.12, U5.2 (QB)
unnamed: J34.14, U5.6 (QC)
unnamed: J34.16, U5.7 (QD)
unnamed: R1.2, SW1.2, U7.2 (TR)
unnamed: RN2.2 (R1), SW13.8
unnamed: RN2.3 (R2), SW13.7
unnamed: RN2.4 (R3), SW13.6
unnamed: RN2.5 (R4), SW13.5
unnamed: RN2.6 (R5), SW13.4
unnamed: RN2.7 (R6), SW13.3
unnamed: RN2.8 (R7), SW13.2
unnamed: RN2.9 (R8), SW13.1
unnamed: U2.11 (~LOAD), U4.11 (~LOAD), U5.11 (~LOAD), U5.13 (~BO), U6.5 (UP)
unnamed: U2.13 (~BO), U4.4 (DOWN)
unnamed: U4.13 (~BO), U5.4 (DOWN)
unnamed: U7.3 (Q), U9.1
unnamed: U8.2, U9.2
unnamed: U9.3, U9.4
unnamed: U9.10, U9.11
unnamed: U9.6, U10.1
unnamed: U9.8, U10.2

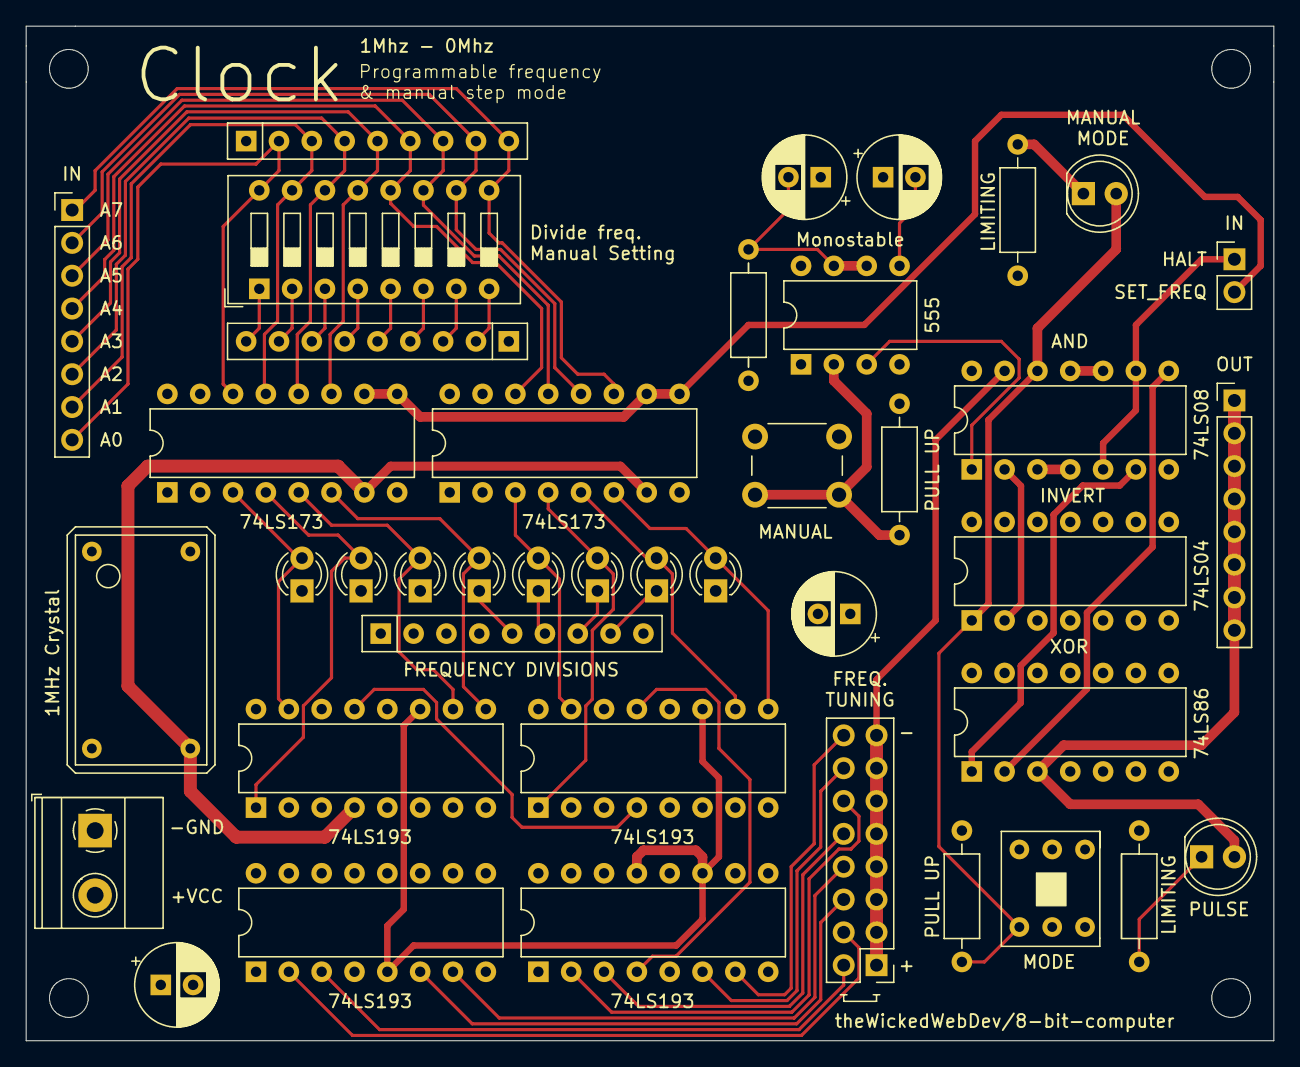
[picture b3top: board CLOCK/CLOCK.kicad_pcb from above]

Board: 4 copper layers, 96.5 x 78.5 mm, 41 parts (0 on the bottom side), 62 nets.

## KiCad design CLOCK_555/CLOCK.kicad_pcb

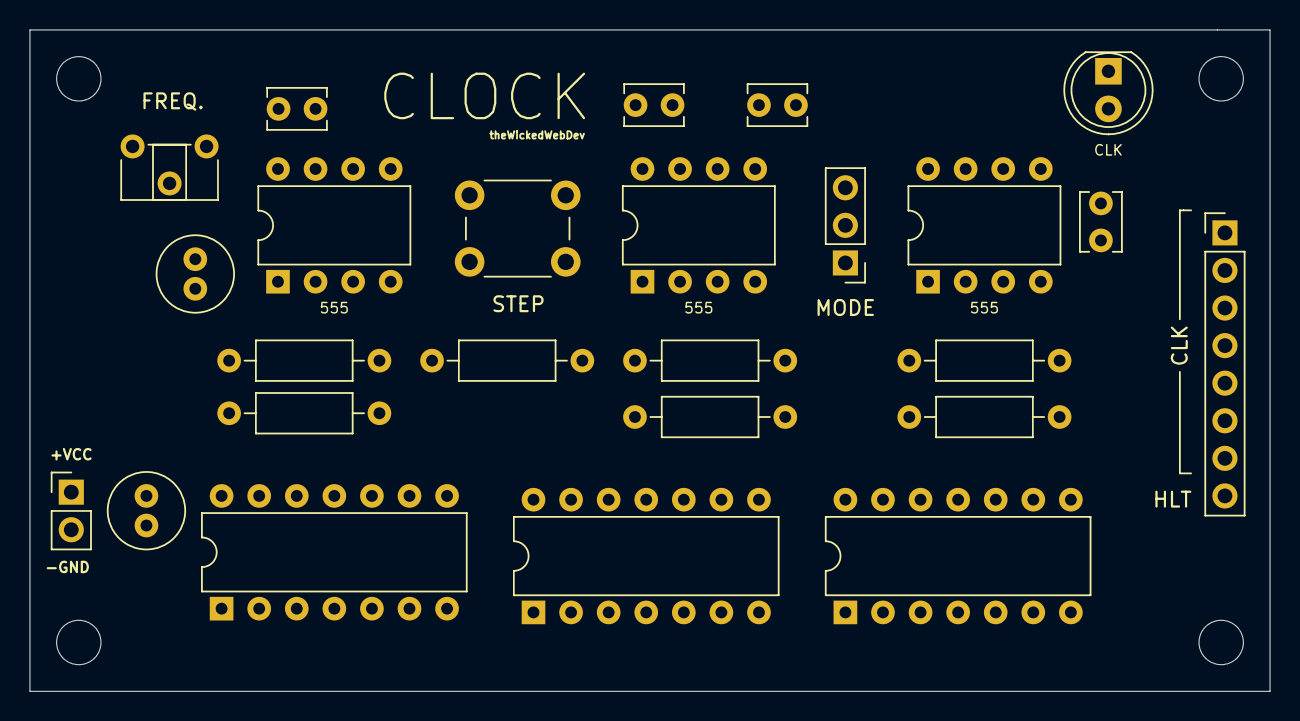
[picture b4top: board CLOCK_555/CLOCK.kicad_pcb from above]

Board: 2 copper layers, 83.8 x 44.7 mm, 25 parts (0 on the bottom side), 21 nets, no tracks yet.

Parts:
C1, C3: CP1; C_Radial_D5.0mm_H11.0mm_P2.00mm
C2, C4, C5, C6: C; C_Disc_D3.8mm_W2.6mm_P2.50mm
D3: LED; LED_D5.0mm
J2: Conn_01x02; PinHeader_1x02_P2.54mm_Vertical
J3: Conn_01x08; PinHeader_1x08_P2.54mm_Vertical
R1, R2, R3, R5, R7, R8, R9: R_US; R_Axial_DIN0207_L6.3mm_D2.5mm_P10.16mm_Horizontal
RV1: R_POT; Potentiometer_ACP_CA6-H2,5_Horizontal
SW1: SW_Push; SW_PUSH_6mm
SW2: SW_SPDT; PinHeader_1x03_P2.54mm_Vertical
U1, U2, U3: NE555P; DIP-8_W7.62mm
U4: 74LS04; DIP-14_W7.62mm
U5: 74LS08; DIP-14_W7.62mm
U6: 74LS32; DIP-14_W7.62mm

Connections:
/CLK: D3.2, J3.1, J3.2, J3.3, J3.4, J3.5, J3.6, J3.7, U5.8
/HLT: J3.8, U4.1
GND: C1.2, C2.2, C3.2, C4.2, C5.2, C6.2, J2.2, R9.1, SW1.1, SW2.2, U1.1, U2.1, U3.1, U3.6, U4.7, U5.7, U6.7
unnamed: C2.1, U1.5
unnamed: C3.1, RV1.1, U1.2, U1.6
unnamed: C4.1, U2.5
unnamed: C5.1, R5.2, U2.3, U2.6, U2.7, U5.5
unnamed: C6.1, R8.2, SW2.3, U3.4
unnamed: D3.1, R9.2
unnamed: R1.2, R2.2, U1.7
unnamed: R2.1, RV1.2
unnamed: R3.2, SW1.2, U2.2
unnamed: R7.2, SW2.1, U3.2
unnamed: U1.3, U5.1
unnamed: U3.3, U4.3, U5.2
unnamed: U4.2, U5.10
unnamed: U4.4, U5.4
unnamed: U5.3, U6.1
unnamed: U5.6, U6.2
unnamed: U5.9, U6.3
VCC: C1.1, J2.1, R1.1, R3.1, R5.1, R7.1, R8.1, U1.4, U1.8, U2.4, U2.8, U3.8, U4.14, U5.14, U6.14
